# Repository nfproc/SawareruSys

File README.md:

SawareruSys: A "touchable" remote FPGA lab system
=================================================
Copyright (C) 2022-2026 Naoki FUJIEDA. All rights reserved.

### 概要

ディジタル回路や FPGA の学習におけるこれまでの遠隔学習システムには，
その操作から実際にハードウェアに触れているとの実感を得ることが難しい，
という問題点がありました．例えば，ACRi ルーム上の仮想マシンには FPGA
ボードが接続されているものの，そのスイッチや LED 等を直接操作・確認
することはできませんでした．

本リポジトリでは，この問題点に対する解決法として開発された，ディジタル
回路の「さわれる」遠隔学習システム SawareruSys のソースコード一式を
公開しています．詳しい学術的背景や，システムの設計・評価については，
以下の文献を参照してください．

N. Fujieda and A. Okuchi. A Novel Remote FPGA Lab Platform Using
MCU-based Controller Board. In 12th International Conference on
Teaching, Assessment and Learning for Engineering (TALE 2023),
pp. 188-193, 2023, DOI: <a href="https://doi.org/10.1109/TALE56641.2023.10398409">
10.1109/TALE56641.2023.10398409</a>.

ユーザ向けの説明は，ユーザマニュアルを参照してください．マニュアルは，
本リポジトリの Manual/main.pdf または配布パッケージの UserManual.pdf
にあります．

配布パッケージのダウンロード:
<a href="https://aitech.ac.jp/~dslab/nf/SawareruSys/SawareruSys_dist_v1_2_0.zip">
ZIP</a> (33.7 MiB)

### 本リポジトリの内容:
- Board/         : コントローラボードの KiCad による設計ファイル一式
  - v2/          : 「FPGA リモコンボード V2」用
  - v4/          : 「FPGA リモコンボード V4」および「SawareruBoard V1」用
- Connector/     : コントローラボードと FPGA ボードとの通信中継アプリ
  - Client/      : PC 側で動作させる Connector アプリ（C# + WPF）
  - Server/      : 遠隔サーバ側で動作させる Connector アプリ（Python）
- DRFront/       : <a href="https://github.com/nfproc/DRFront">DRFront</a>
- Manual/        : ユーザマニュアルの LaTeX ソース一式
- PIC/           : コントローラボード上の PIC 制御プログラム（C）
  - RemoCon_v2.X : 「FPGA リモコンボード V2」用
  - RemoCon_v4.X : 「FPGA リモコンボード V4」および「SawareruBoard V1」用
- svinst_port/   : <a href="https://github.com/nfproc/svinst_port">svinst_port</a>

### 動作環境
- PC 側: Windows 10 以降 + .NET Framework 4.8
- サーバ側: Ubuntu 20.04 LTS 以降 + Python 3.8 以降 + Vivado 2020.2 以降

配布パッケージをビルドする際には，msbuild と Rust (cargo) も必要です．
msbuild 17.14.40 (Visual Studio 2022) および cargo 1.93.1 の環境で
ビルドできることを確認しています．

### 配布パッケージのビルド
配布パッケージのビルドは，PowerShell スクリプト Generate_Dist.ps1
により自動的に行います．このスクリプトは，作業フォルダとして Build，
Dist，Pkg の3つのフォルダを作成し，SawareruSys の配布パッケージを
SawareruSys_dist.zip，DRFront の配布パッケージを DRFront_dist.zip
として，それぞれ保存します．

### ライセンス
サブモジュール（DRFront と svinst_port），および PIC/RemoCon_v2.x
フォルダの `usb_` で始まるファイルを**除く**各ファイルには，New BSD
ライセンスが適用されます．

また，SawareruSys の配布パッケージには以下のソフトウェアが含まれ，
それぞれのライセンスに従ってバイナリを再配布しています．
- DRFront: New BSD ライセンス
- Ookii.Dialogs.Wpf: New BSD ライセンス
- svinst_port: MIT ライセンス
- WinSCP: GPL v3 ライセンス

PIC/RemoCon_v2.x フォルダの `usb_` で始まるファイル群は，Microchip
USB ライブラリの一部であり，Microchip 社の著作物です．これらには
Apache ライセンス v2.0 が適用されます．

詳細は COPYING ファイルを参照してください．

### 更新履歴

- v1.2.0 2026-03-04
  - DRFront のバージョンを 0.7.0 に更新．
  - 再配布する WinSCP のバージョンを 6.5.5 に更新．
  - 上記更新に伴うビルドスクリプトの修正．

- v1.1.0 2025-05-08
  - DRFront のバージョンを 0.6.0 に更新．
  - 上記更新に伴うビルドスクリプトの修正．

- v1.0.1 2024-05-06
  - DRFront のバージョンを 0.5.1 に更新．
  - 配布パッケージをビルドする際，前回作成した zip ファイルを上書き
    するように変更．

- v1.0.0 2024-04-03
  - 最初のバージョン．

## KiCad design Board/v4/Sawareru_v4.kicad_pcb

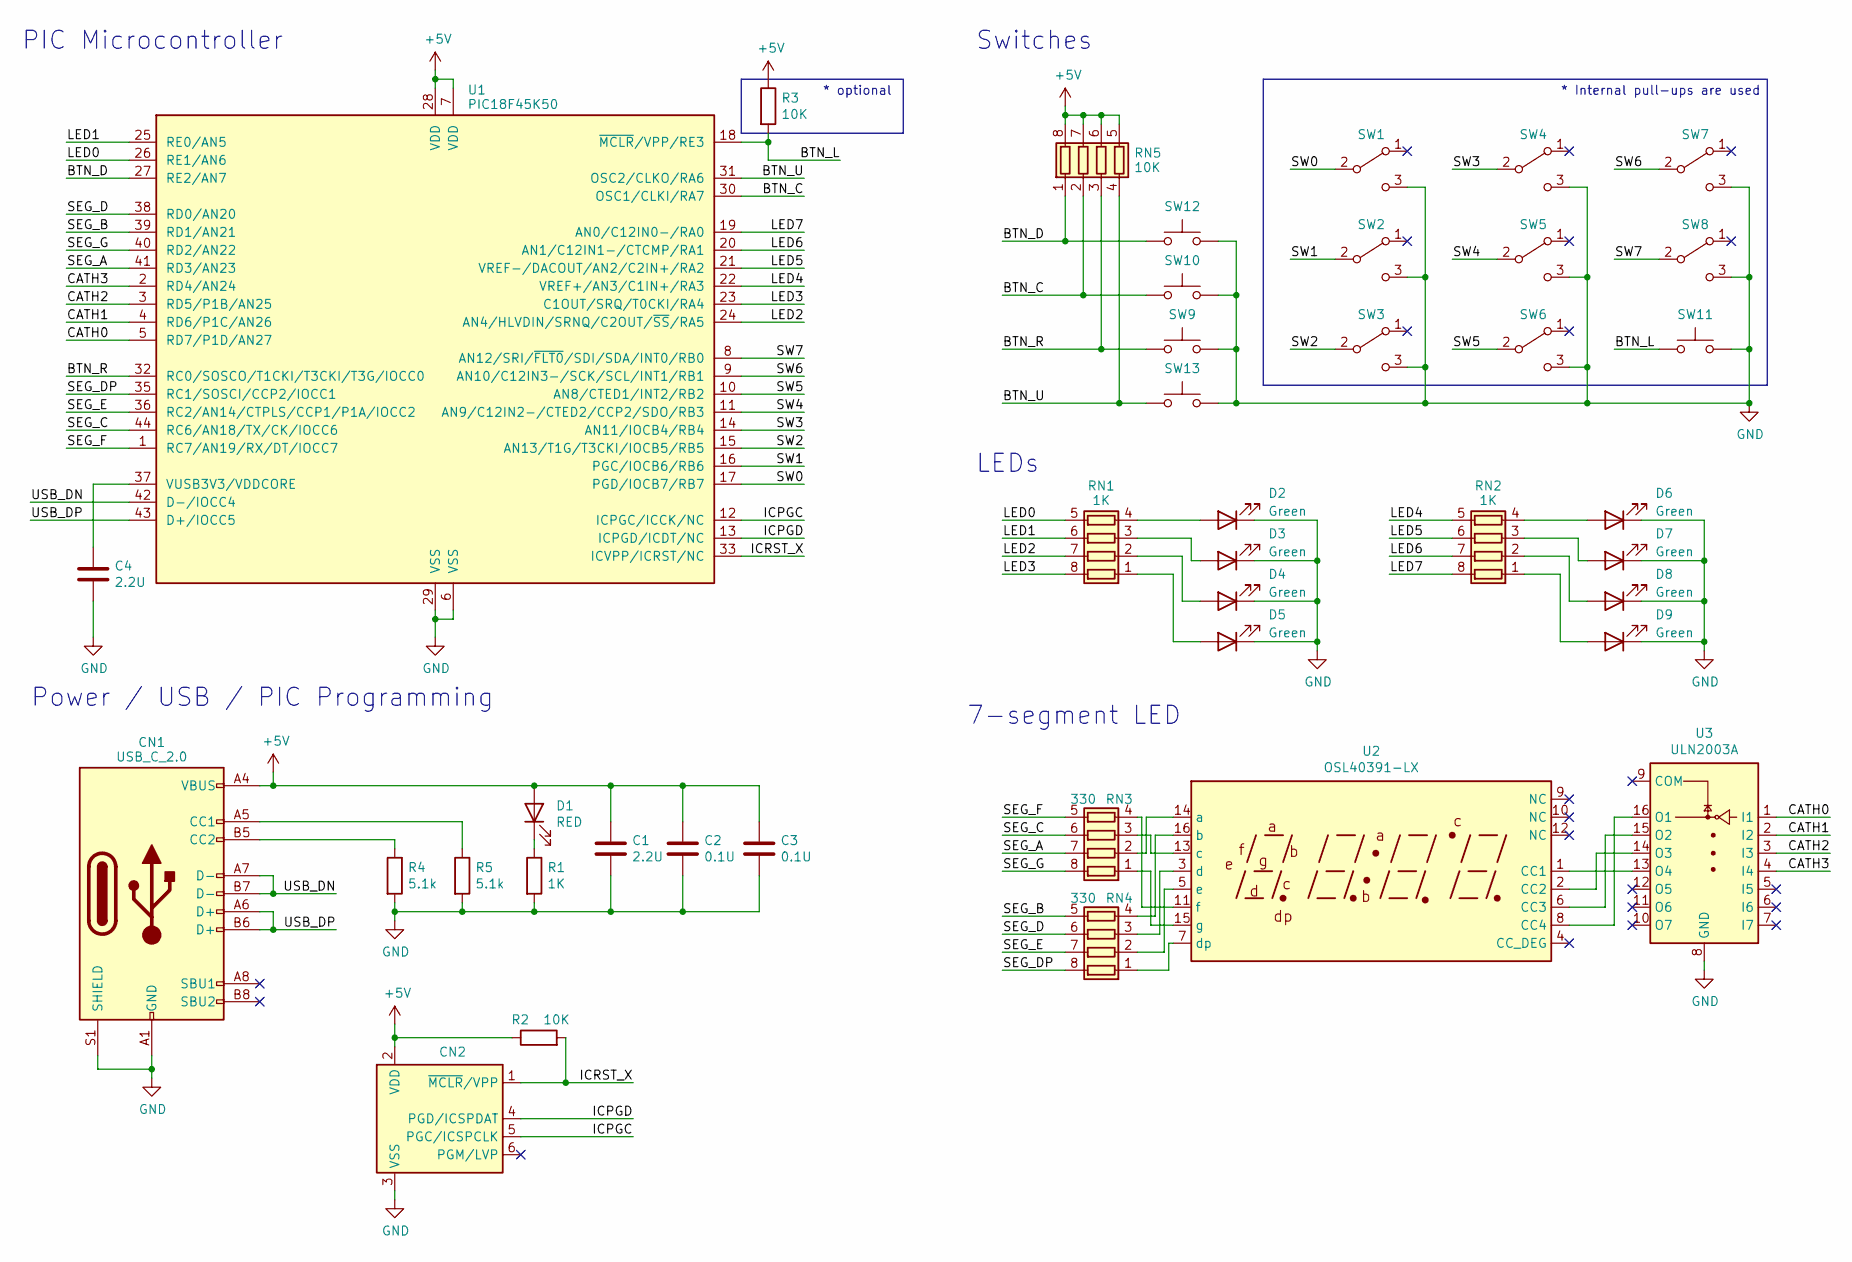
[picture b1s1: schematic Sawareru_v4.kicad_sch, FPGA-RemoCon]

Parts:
C1: 2.2U; USB_C_Receptacle_HRO_TYPE-C-31-M-12
C2, C3: 0.1U; C_0603_1608Metric_Pad1.08x0.95mm_HandSolder
C4: 2.2U; C_0603_1608Metric_Pad1.08x0.95mm_HandSolder
CN1: USB_C_2.0; USB_HRO_TYPE-C-31-M-12
CN2: Conn_PIC_ICSP_ICD; PinHeader_1x06_P2.54mm_Vertical
D1: RED; LED_0603_1608Metric_Pad1.05x0.95mm_HandSolder
D2, D3, D4, D5, D6, D7, D8, D9: Green; LED_0603_1608Metric_Pad1.05x0.95mm_HandSolder
R1: 1K; R_0603_1608Metric_Pad0.98x0.95mm_HandSolder
R2, R3: 10K; R_0603_1608Metric_Pad0.98x0.95mm_HandSolder
R4, R5: 5.1k; R_0603_1608Metric_Pad0.98x0.95mm_HandSolder
RN1, RN2: 1K; R_Array_Convex_4x0603
RN3, RN4: 330; R_Array_Convex_4x0603
RN5: 10K; R_Array_Convex_4x0603
SW1, SW2, SW3, SW4, SW5, SW6, SW7, SW8: SW_SPDT; SW_Slide_SSSS213202
SW9, SW10, SW11, SW12, SW13: SW_Push; SW_SPST_TS-06104
U1: PIC18F45K50; TQFP-44_10x10mm_P0.8mm
U2: OSL40391-LX; OSL40391
U3: ULN2003A; SOIC-16_3.9x9.9mm_P1.27mm

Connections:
+5V: C1.1, C2.1, C3.1, CN1.A4 (VBUS), CN1.A9 (VBUS), CN1.B4 (VBUS), CN1.B9 (VBUS), CN2.2 (VDD), D1.2 (A), R2.1, R3.1, RN5.5 (R4.2), RN5.6 (R3.2), RN5.7 (R2.2), RN5.8 (R1.2), U1.7 (VDD), U1.28 (VDD)
/BTN_C: RN5.2 (R2.1), SW10.1, U1.30 (OSC1/CLKI/RA7)
/BTN_D: RN5.1 (R1.1), SW12.1, U1.27 (RE2/AN7)
/BTN_L: R3.2, SW11.1, U1.18 (~MCLR/VPP/RE3)
/BTN_R: RN5.3 (R3.1), SW9.1, U1.32 (RC0/SOSCO/T1CKI/T3CKI/T3G/IOCC0)
/BTN_U: RN5.4 (R4.1), SW13.1, U1.31 (OSC2/CLKO/RA6)
/CATH0: U1.5 (RD7/P1D/AN27), U3.1 (I1)
/CATH1: U1.4 (RD6/P1C/AN26), U3.2 (I2)
/CATH2: U1.3 (RD5/P1B/AN25), U3.3 (I3)
/CATH3: U1.2 (RD4/AN24), U3.4 (I4)
/ICPGC: CN2.5 (PGC/ICSPCLK), U1.12 (ICPGC/ICCK/NC)
/ICPGD: CN2.4 (PGD/ICSPDAT), U1.13 (ICPGD/ICDT/NC)
/ICRST_X: CN2.1 (~MCLR/VPP), R2.2, U1.33 (ICVPP/ICRST/NC)
/LED0: RN1.5 (R4.2), U1.26 (RE1/AN6)
/LED1: RN1.6 (R3.2), U1.25 (RE0/AN5)
/LED2: RN1.7 (R2.2), U1.24 (AN4/HLVDIN/SRNQ/C2OUT/~SS/RA5)
/LED3: RN1.8 (R1.2), U1.23 (C1OUT/SRQ/T0CKI/RA4)
/LED4: RN2.5 (R4.2), U1.22 (VREF+/AN3/C1IN+/RA3)
/LED5: RN2.6 (R3.2), U1.21 (VREF-/DACOUT/AN2/C2IN+/RA2)
/LED6: RN2.7 (R2.2), U1.20 (AN1/C12IN1-/CTCMP/RA1)
/LED7: RN2.8 (R1.2), U1.19 (AN0/C12IN0-/RA0)
/SEG_A: RN3.7 (R2.2), U1.41 (RD3/AN23)
/SEG_B: RN4.5 (R4.2), U1.39 (RD1/AN21)
/SEG_C: RN3.6 (R3.2), U1.44 (RC6/AN18/TX/CK/IOCC6)
/SEG_D: RN4.6 (R3.2), U1.38 (RD0/AN20)
/SEG_DP: RN4.8 (R1.2), U1.35 (RC1/SOSCI/CCP2/IOCC1)
/SEG_E: RN4.7 (R2.2), U1.36 (RC2/AN14/CTPLS/CCP1/P1A/IOCC2)
/SEG_F: RN3.5 (R4.2), U1.1 (RC7/AN19/RX/DT/IOCC7)
/SEG_G: RN3.8 (R1.2), U1.40 (RD2/AN22)
/SW0: SW1.2 (B), U1.17 (PGD/IOCB7/RB7)
/SW1: SW2.2 (B), U1.16 (PGC/IOCB6/RB6)
/SW2: SW3.2 (B), U1.15 (AN13/T1G/T3CKI/IOCB5/RB5)
/SW3: SW4.2 (B), U1.14 (AN11/IOCB4/RB4)
/SW4: SW5.2 (B), U1.11 (AN9/C12IN2-/CTED2/CCP2/SDO/RB3)
/SW5: SW6.2 (B), U1.10 (AN8/CTED1/INT2/RB2)
/SW6: SW7.2 (B), U1.9 (AN10/C12IN3-/SCK/SCL/INT1/RB1)
/SW7: SW8.2 (B), U1.8 (AN12/SRI/~FLT0/SDI/SDA/INT0/RB0)
/USB_DN: CN1.A7 (D-), CN1.B7 (D-), U1.42 (D-/IOCC4)
/USB_DP: CN1.A6 (D+), CN1.B6 (D+), U1.43 (D+/IOCC5)
GND: C1.2, C2.2, C3.2, C4.2, CN1.A1 (GND), CN1.A12 (GND), CN1.B1 (GND), CN1.B12 (GND), CN1.S1 (SHIELD), CN2.3 (VSS), D2.1 (K), D3.1 (K), D4.1 (K), D5.1 (K), D6.1 (K), D7.1 (K), D8.1 (K), D9.1 (K), R1.2, R4.2, R5.2, SW1.3 (C), SW2.3 (C), SW3.3 (C), SW4.3 (C), SW5.3 (C), SW6.3 (C), SW7.3 (C), SW8.3 (C), SW9.2, SW10.2, SW11.2, SW12.2, SW13.2, U1.6 (VSS), U1.29 (VSS), U3.8 (GND)
unnamed: CN1.A5 (CC1), R5.1
unnamed: CN1.B5 (CC2), R4.1
unnamed: D1.1 (K), R1.1
unnamed: D2.2 (A), RN1.4 (R4.1)
unnamed: D3.2 (A), RN1.3 (R3.1)
unnamed: D4.2 (A), RN1.2 (R2.1)
unnamed: D5.2 (A), RN1.1 (R1.1)
unnamed: D6.2 (A), RN2.4 (R4.1)
unnamed: D7.2 (A), RN2.3 (R3.1)
unnamed: D8.2 (A), RN2.2 (R2.1)
unnamed: D9.2 (A), RN2.1 (R1.1)
unnamed: RN3.1 (R1.1), U2.15 (g)
unnamed: RN3.2 (R2.1), U2.14 (a)
unnamed: RN3.3 (R3.1), U2.13 (c)
unnamed: RN3.4 (R4.1), U2.11 (f)
unnamed: RN4.1 (R1.1), U2.7 (dp)
unnamed: RN4.2 (R2.1), U2.5 (e)
unnamed: RN4.3 (R3.1), U2.3 (d)
unnamed: RN4.4 (R4.1), U2.16 (b)
unnamed: C4.1, U1.37 (VUSB3V3/VDDCORE)
unnamed: U2.1 (CC1), U3.13 (O4)
unnamed: U2.2 (CC2), U3.14 (O3)
unnamed: U2.6 (CC3), U3.15 (O2)
unnamed: U2.8 (CC4), U3.16 (O1)

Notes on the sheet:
Switches
* Internal pull-ups are used
PIC Microcontroller
Power / USB / PIC Programming
7-segment LED
* optional
LEDs

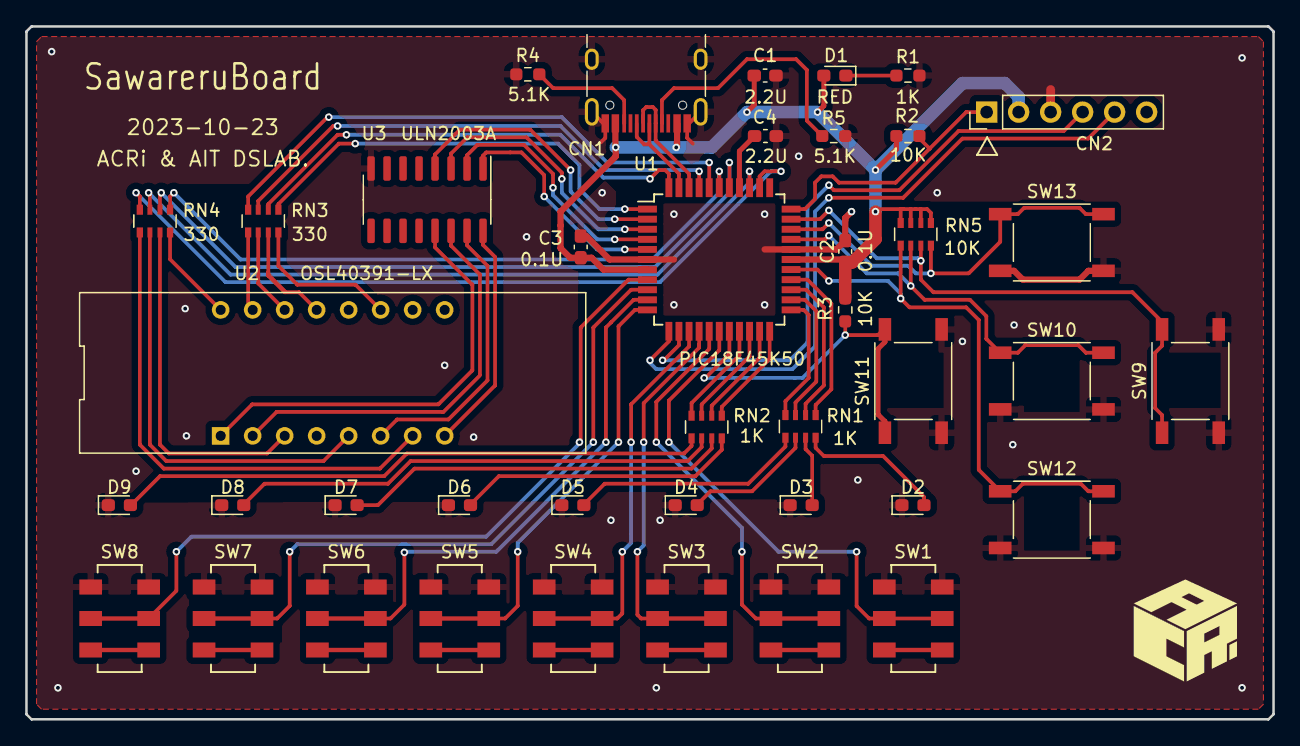
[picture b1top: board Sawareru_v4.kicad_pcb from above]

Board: 2 copper layers, 99.0 x 55.0 mm, 41 parts (0 on the bottom side), 64 nets.

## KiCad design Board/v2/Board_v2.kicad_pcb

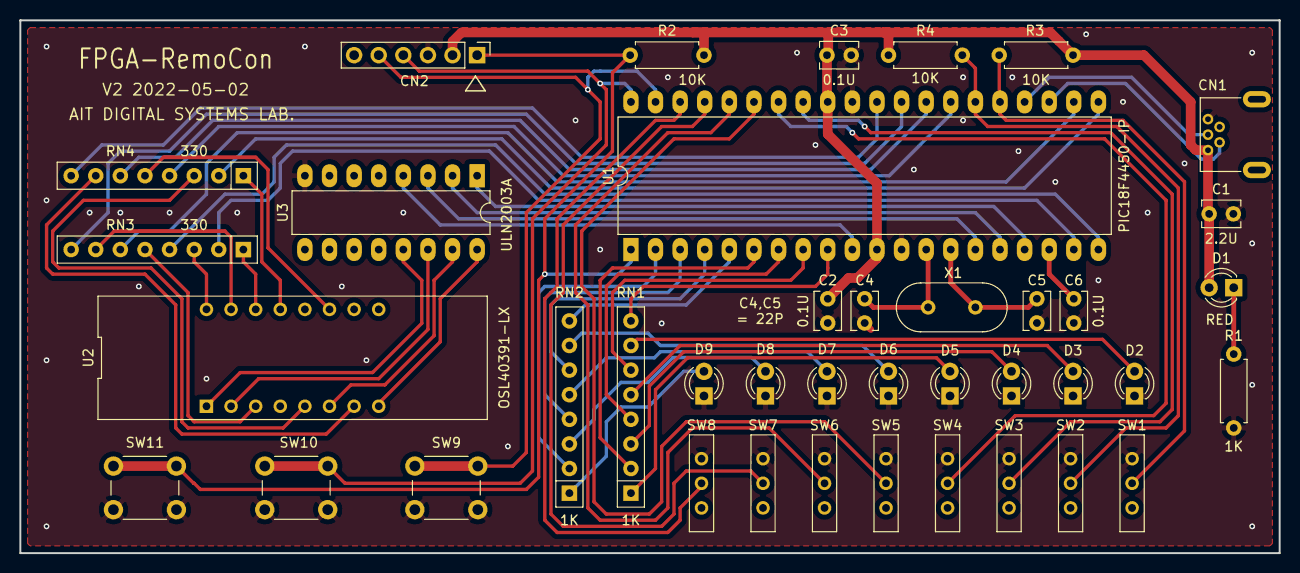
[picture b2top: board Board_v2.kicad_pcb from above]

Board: 2 copper layers, 130.0 x 55.0 mm, 40 parts (0 on the bottom side), 59 nets.

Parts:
C1: 2.2U; C_Disc_D3.8mm_W2.6mm_P2.50mm
C2, C3, C6: 0.1U; C_Disc_D3.8mm_W2.6mm_P2.50mm
C4, C5: 22p; C_Disc_D3.8mm_W2.6mm_P2.50mm
CN1: USB_B_Mini; USB_MiniB_TE_2172034-1
CN2: Conn_PIC_ICSP_ICD; PinHeader_1x06_P2.54mm_Vertical
D1: RED; LED_D3.0mm
D2, D3, D4, D5, D6, D7, D8, D9: Green; LED_D3.0mm
R1: 1K; R_Axial_DIN0207_L6.3mm_D2.5mm_P7.62mm_Horizontal
R2, R3, R4: 10K; R_Axial_DIN0207_L6.3mm_D2.5mm_P7.62mm_Horizontal
RN1, RN2: 1K; R_Array_SIP8
RN3, RN4: 330; R_Array_SIP8
SW1, SW2, SW3, SW4, SW5, SW6, SW7, SW8: SW_SPDT; SW_Slide_MSS102545
SW9, SW10, SW11: SW_Push; SW_PUSH_6mm_H5mm
U1: PIC18F4450-IP; DIP-40_W15.24mm_LongPads
U2: OSL40391-LX; OSL40391
U3: ULN2003A; DIP-16_W7.62mm_LongPads
X1: 16MHz; Crystal_HC49-4H_Vertical

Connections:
+5V: C1.1, C2.1, C3.1, CN1.1, CN2.2, D1.2, R2.1, R3.1, R4.1, U1.11, U1.32
/BTN0_PGC: CN2.5, SW9.1, U1.39
/BTN1_PGD: CN2.4, SW10.1, U1.40
/BTN2_MCLR: CN2.1, R2.2, SW11.1, U1.1
/CATH0: U1.17, U3.1
/CATH1: U1.16, U3.2
/CATH2: U1.15, U3.3
/CATH3: U1.10, U3.4
/LED0: RN1.8, U1.9
/LED1: RN1.6, U1.8
/LED2: RN1.4, U1.7
/LED3: RN1.2, U1.6
/LED4: RN2.8, U1.5
/LED5: RN2.6, U1.4
/LED6: RN2.4, U1.3
/LED7: RN2.2, U1.2
/SEG_A: RN3.2, U1.19
/SEG_B: RN3.4, U1.20
/SEG_C: RN4.2, U1.21
/SEG_D: RN3.6, U1.22
/SEG_DP: RN4.8, U1.30
/SEG_E: RN4.4, U1.27
/SEG_F: RN4.6, U1.28
/SEG_G: RN3.8, U1.29
/SW0: R3.2, SW1.2, U1.25
/SW1: R4.2, SW2.2, U1.26
/SW2: SW3.2, U1.33
/SW3: SW4.2, U1.34
/SW4: SW5.2, U1.35
/SW5: SW6.2, U1.36
/SW6: SW7.2, U1.37
/SW7: SW8.2, U1.38
/USB_DN: CN1.2, U1.23
/USB_DP: CN1.3, U1.24
GND: C1.2, C2.2, C3.2, C4.2, C5.2, C6.2, CN1.5, CN2.3, D2.1, D3.1, D4.1, D5.1, D6.1, D7.1, D8.1, D9.1, R1.2, SW1.3, SW2.3, SW3.3, SW4.3, SW5.3, SW6.3, SW7.3, SW8.3, SW9.2, SW10.2, SW11.2, U1.12, U1.31, U3.8
unnamed: C4.1, U1.13, X1.2
unnamed: C5.1, U1.14, X1.1
unnamed: C6.1, U1.18
unnamed: D1.1, R1.1
unnamed: D2.2, RN1.7
unnamed: D3.2, RN1.5
unnamed: D4.2, RN1.3
unnamed: D5.2, RN1.1
unnamed: D6.2, RN2.7
unnamed: D7.2, RN2.5
unnamed: D8.2, RN2.3
unnamed: D9.2, RN2.1
unnamed: RN3.1, U2.14
unnamed: RN3.3, U2.16
unnamed: RN3.5, U2.3
unnamed: RN3.7, U2.15
unnamed: RN4.1, U2.13
unnamed: RN4.3, U2.5
unnamed: RN4.5, U2.11
unnamed: RN4.7, U2.7
unnamed: U2.1, U3.13
unnamed: U2.2, U3.14
unnamed: U2.6, U3.15
unnamed: U2.8, U3.16

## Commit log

2024-04-03 v1.0.0: first commit!
2024-05-06 v1.0.1: correct issues of DRFront and build script
2025-05-08 v1.1.0: DRFront now supports workflow without .dcp files
2026-03-04 v1.2.0: DRFront now supports VHDL-2008
